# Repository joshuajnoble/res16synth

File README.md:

# res16synth

These boards are for a workshop I ran at Resonate 2016 called "Volt, Amp, Synth & Sound"

I really wanted to make a simple workshop about electronics that all beginners could understand. It was a fun little exercise in making an intuitive and approachable way to learn something that is usually thought of as difficult.

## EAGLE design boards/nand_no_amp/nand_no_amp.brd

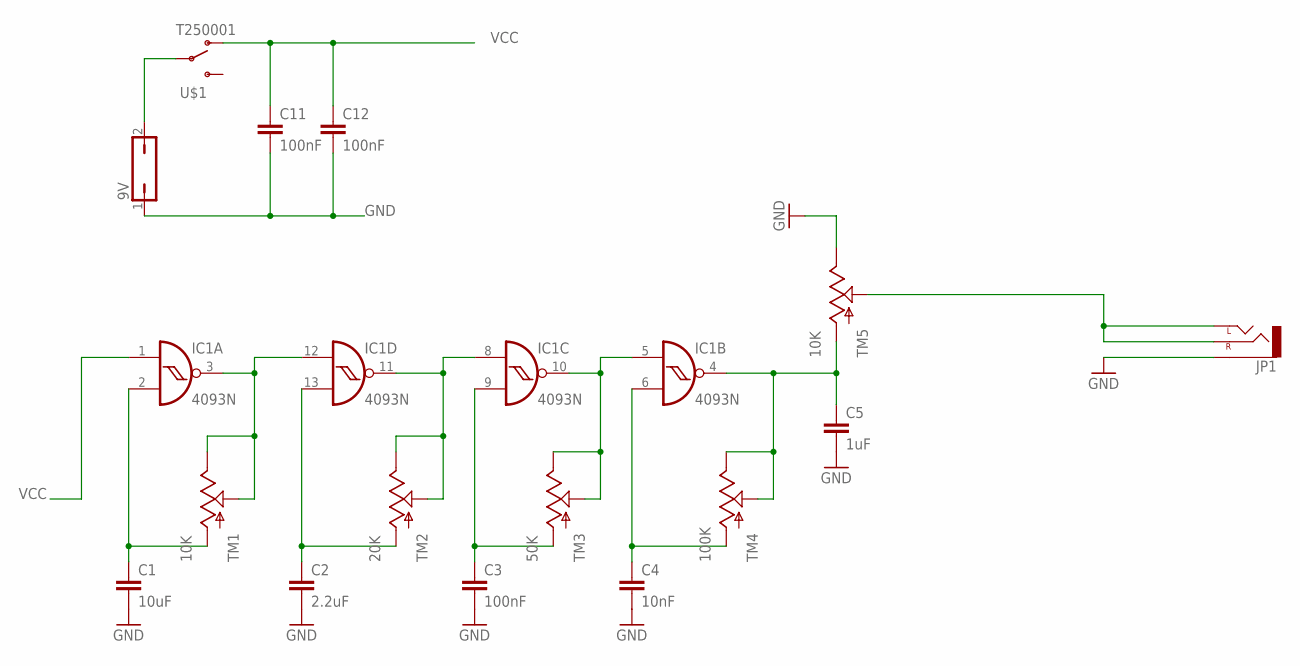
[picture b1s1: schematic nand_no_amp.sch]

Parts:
9V: JP1Q; JP1
C1: 10uF; CAP-PTH-5MM
C2: 2.2uF; CAP-PTH-5MM
C3: 100nF; CAP-PTH-5MM
C4: 10nF; CAP-PTH-5MM
C5: 1uF; CAP-PTH-5MM
C11, C12: 100nF; CAP-PTH-SMALL
IC1: 4093N; DIL14
JP1: AUDIO-JACKPTH; AUDIO-JACK
TM1, TM5: 10K; 296SERIESPOT
TM2: 20K; 296SERIESPOT
TM3: 50K; 296SERIESPOT
TM4: 100K; 296SERIESPOT
U$1: T250001

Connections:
AUDIO_OUT: JP1.RING (RIGHT), JP1.TIP (LEFT), TM5.PIN2 (S)
GND: 9V.1, C1.2, C2.2, C3.2, C4.2, C5.2, C11.2, C12.2, JP1.SLEEVE, TM5.PIN3 (E)
unnamed: IC1.3 (O), IC1.12 (I0), TM1.PIN2 (S), TM1.PIN3 (E)
unnamed: IC1.8 (I0), IC1.11 (O), TM2.PIN2 (S), TM2.PIN3 (E)
unnamed: IC1.5 (I0), IC1.10 (O), TM3.PIN2 (S), TM3.PIN3 (E)
unnamed: C1.1, IC1.2 (I1), TM1.PIN1 (A)
unnamed: C2.1, IC1.13 (I1), TM2.PIN1 (A)
unnamed: C3.1, IC1.9 (I1), TM3.PIN1 (A)
unnamed: C4.1, IC1.6 (I1), TM4.PIN1 (A)
unnamed: C5.1, IC1.4 (O), TM4.PIN2 (S), TM4.PIN3 (E), TM5.PIN1 (A)
unnamed: 9V.2, U$1.5
VCC: C11.1, C12.1, IC1.1 (I0), IC1.14 (VDD), U$1.4 (O)
VSS: IC1.7 (VSS)

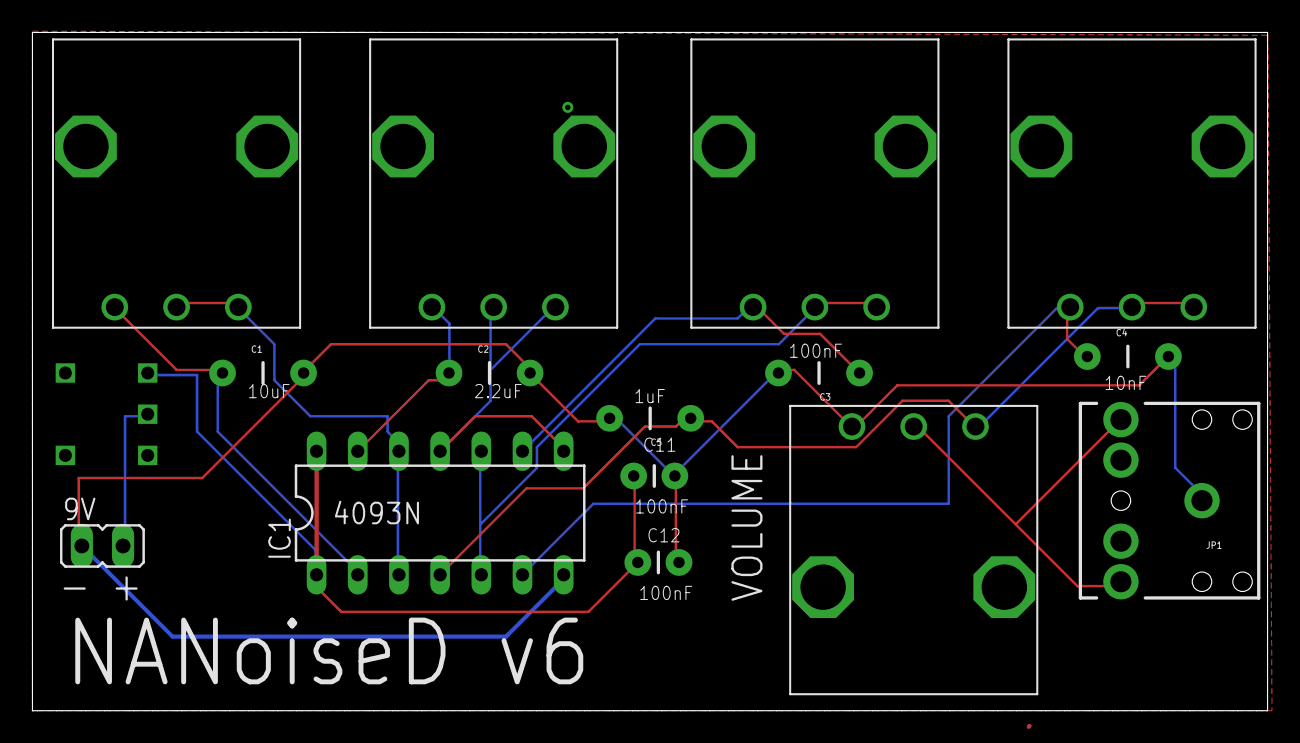
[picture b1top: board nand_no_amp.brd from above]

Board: 2 copper layers, 76.2 x 41.8 mm, 16 parts (0 on the bottom side), 12 nets.

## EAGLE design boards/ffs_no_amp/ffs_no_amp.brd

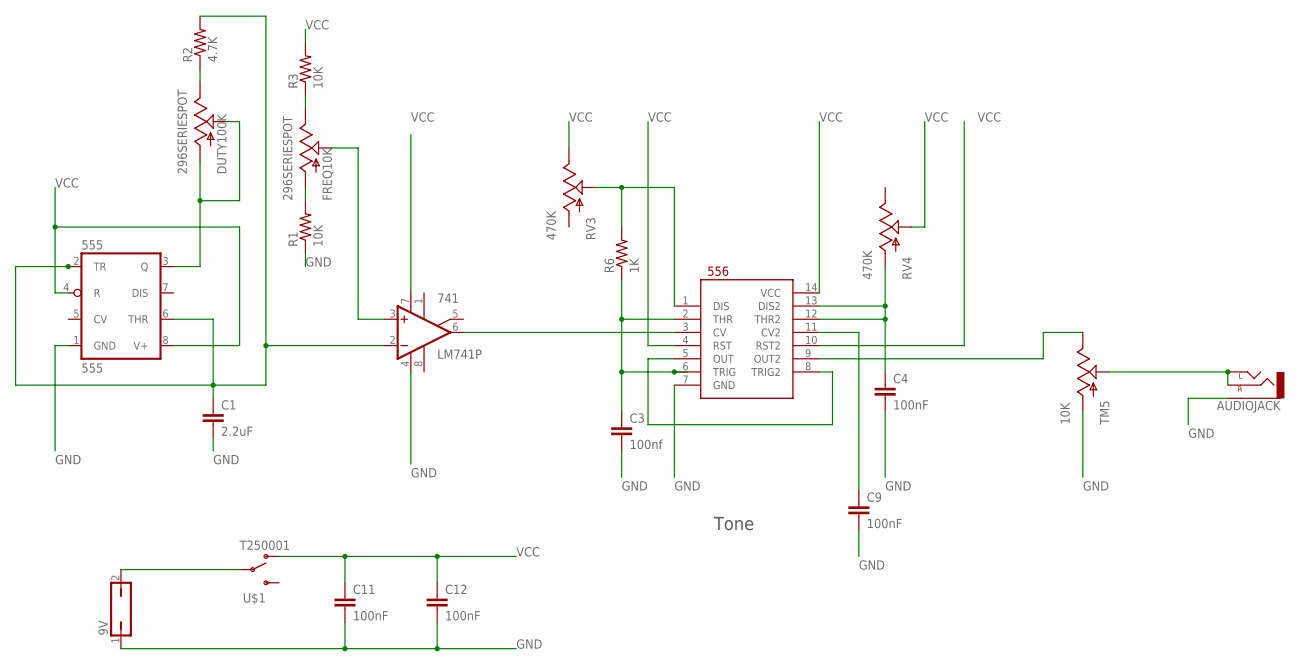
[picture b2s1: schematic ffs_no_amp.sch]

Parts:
9V: JP1Q; JP1
555: 555; DIL08-ROUND
556: 556; DIL14
741: LM741P; DIL08
AUDIOJACK: AUDIO-JACKPTH; AUDIO-JACK
C1: 2.2uF; CAP-PTH-5MM
C3: 100nf; CAP-PTH-SMALL
C4, C9, C11, C12: 100nF; CAP-PTH-SMALL
DUTY100K: 296SERIESPOT
FREQ10K: 296SERIESPOT
R1, R3: 10K; AXIAL-0.4
R2: 4.7K; AXIAL-0.4
R6: 1K; AXIAL-0.4
RV3, RV4: 470K; 296SERIESPOT
TM5: 10K; 296SERIESPOT
U$1: T250001

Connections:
BATT: 9V.2, U$1.5
GND: 9V.1, 555.1 (GND), 556.7 (GND), 741.4 (V-), AUDIOJACK.SLEEVE, C1.2, C3.2, C4.2, C9.2, C11.2, C12.2, R1.P$1 (1), TM5.PIN1 (A)
unnamed: 555.2 (TR), 555.6 (THR), 741.2 (-IN), C1.1, R2.P$2 (2)
unnamed: 556.9 (OUT2), TM5.PIN3 (E)
unnamed: FREQ10K.PIN3 (E), R3.P$1 (1)
unnamed: AUDIOJACK.RING (RIGHT), AUDIOJACK.TIP (LEFT), TM5.PIN2 (S)
unnamed: FREQ10K.PIN1 (A), R1.P$2 (2)
unnamed: 556.1 (DIS), R6.P$2 (2), RV3.PIN2 (S)
unnamed: 556.3 (CV), 741.6 (OUT)
unnamed: 556.2 (THR), 556.6 (TRIG), C3.1, R6.P$1 (1)
unnamed: 556.5 (OUT), 556.8 (TRIG2)
unnamed: 556.12 (THR2), 556.13 (DIS2), C4.1, RV4.PIN1 (A)
unnamed: 556.11 (CV2), C9.1
unnamed: 555.3 (Q), DUTY100K.PIN1 (A), DUTY100K.PIN2 (S)
unnamed: DUTY100K.PIN3 (E), R2.P$1 (1)
unnamed: 741.3 (+IN), FREQ10K.PIN2 (S)
VCC: 555.4 (R), 555.8 (V+), 556.4 (RST), 556.10 (RST2), 556.14 (VCC), 741.7 (V+), C11.1, C12.1, R3.P$2 (2), RV3.PIN3 (E), RV4.PIN2 (S), U$1.4 (O)

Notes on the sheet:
Tone

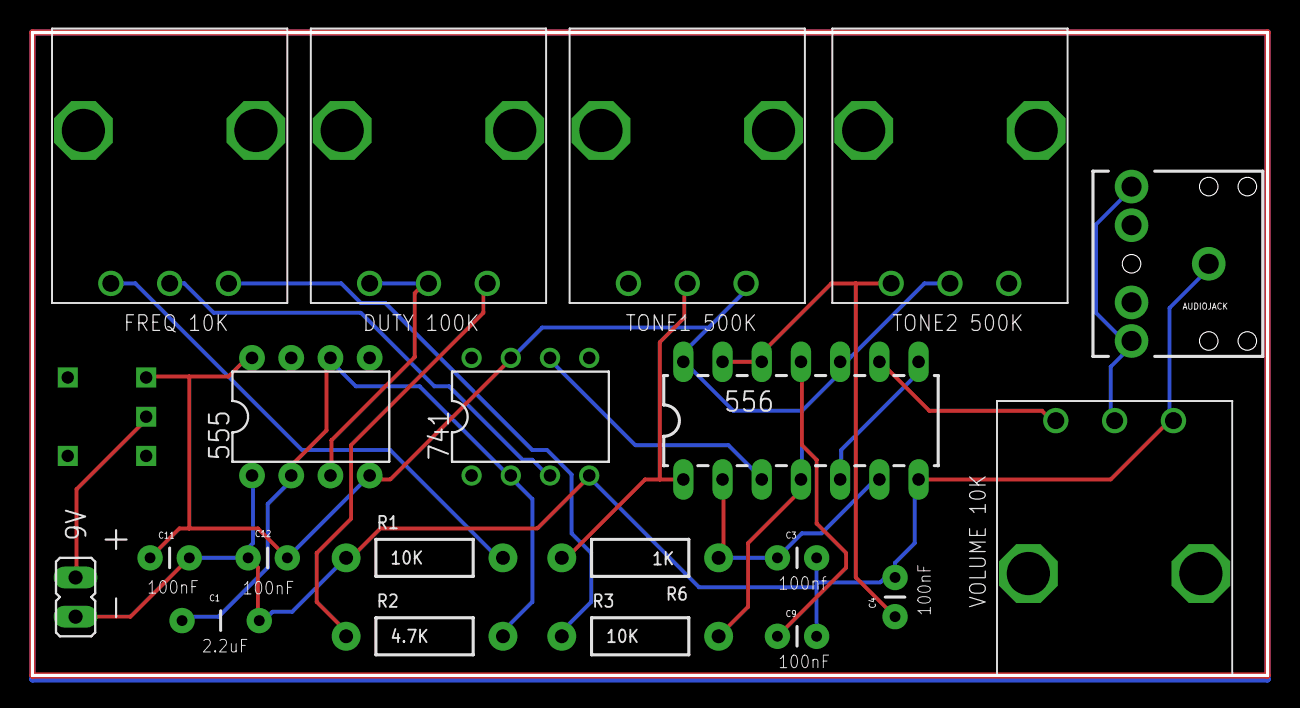
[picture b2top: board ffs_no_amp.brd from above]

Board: 2 copper layers, 80.0 x 41.7 mm, 21 parts (0 on the bottom side), 17 nets.

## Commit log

2016-04-10 adding boards
2016-07-25 adding pngs

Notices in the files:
parts and their libraries:
SparkFun-AnalogIC: Licensing:Creative Commons ShareAlike 4.0 International - https://creativecommons.org/licenses/by-sa/4.0
